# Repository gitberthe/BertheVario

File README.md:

# Projets BertheVario/GnuVario, BertheVarioTac et BertheVario213. 
Vario Gps parapente developés en C/C++ sous Platformio/VisualStudioCode/Code::Blocks (Software). kicad/freecad (Hardware).

**BertheVario/GnuVario :**
- firmware pour GnuVario (https://prunkdump.github.io/GNUVario-TTGO-T5-website/0-Accueil.html)
- carte mere indisponible donc pour mise a jour vario existant uniquement.
- socle pour les fichiers commun des 3 vario.

**BertheVarioTac :**
- Vario a base de ESP32-2432S028 sans la coque.
- un peut lourd pour voler et moindre autonomie d'alimentation.

**BertheVario213 :**
- Vario et coque imprimable 3d a base de Lilygo GDEM0213T5BN.
- le plus abouti des 3 vario.

**Photo des 3 vario :**

**Logiciels annexes :**
- CompZoneAerienne : logiciel pour la creation du fichier de zone aerienne (TMA, CTR...). Visualisation des zones par fichier *.png et *.kml :
- GestHgt : logiciel pour les fichier *.hgt d'altitude sol (filtre france) et creation/verification checksum.
- IgcReader : logiciel pour relire succinctement un fichier igc (Z deco, Z attero ...) et le transformer en .kml pour googleearth.
- igc2kmz : logiciel python disponible sur le web pour creer un fichier .kmz googleearth, a partir d'un .igc (couleur fonction de Vz, altitude...) :

zenodo :
https://doi.org/10.5281/zenodo.18722633

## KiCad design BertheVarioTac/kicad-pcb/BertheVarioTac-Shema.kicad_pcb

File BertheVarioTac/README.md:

# Projet BertheVarioTac ESP32-2432S028
Projet d'alti vario gps parapente tactile (avec gestion des TMA CTR..., et mode guidage sol pour randonnée).
- Code C++ Visual Studio/PlateformIO.
- Plateforme Espressif ESP32 Dev Module, 2.8inch ESP32-2432S028, Arduino, ESP32-WROOM-32,  (processeur LX6 32bits, bi-core 240mhz).

**Utilisation / description :**
- documentation utilisateur et autre dans /documentation
- projet PlateformIO dans /BertheVarioTacPlatformIO
- editer/modifier avec codeblocks dans /Codeblocks
- documentation developpeur dans ../../DoxyBertheVarioTac avec le commande "doxygen Doxyfile.BertheVarioTac" depuis /Codeblocks

**Pour les développeur :**
- voir la documentation doxygen generée.

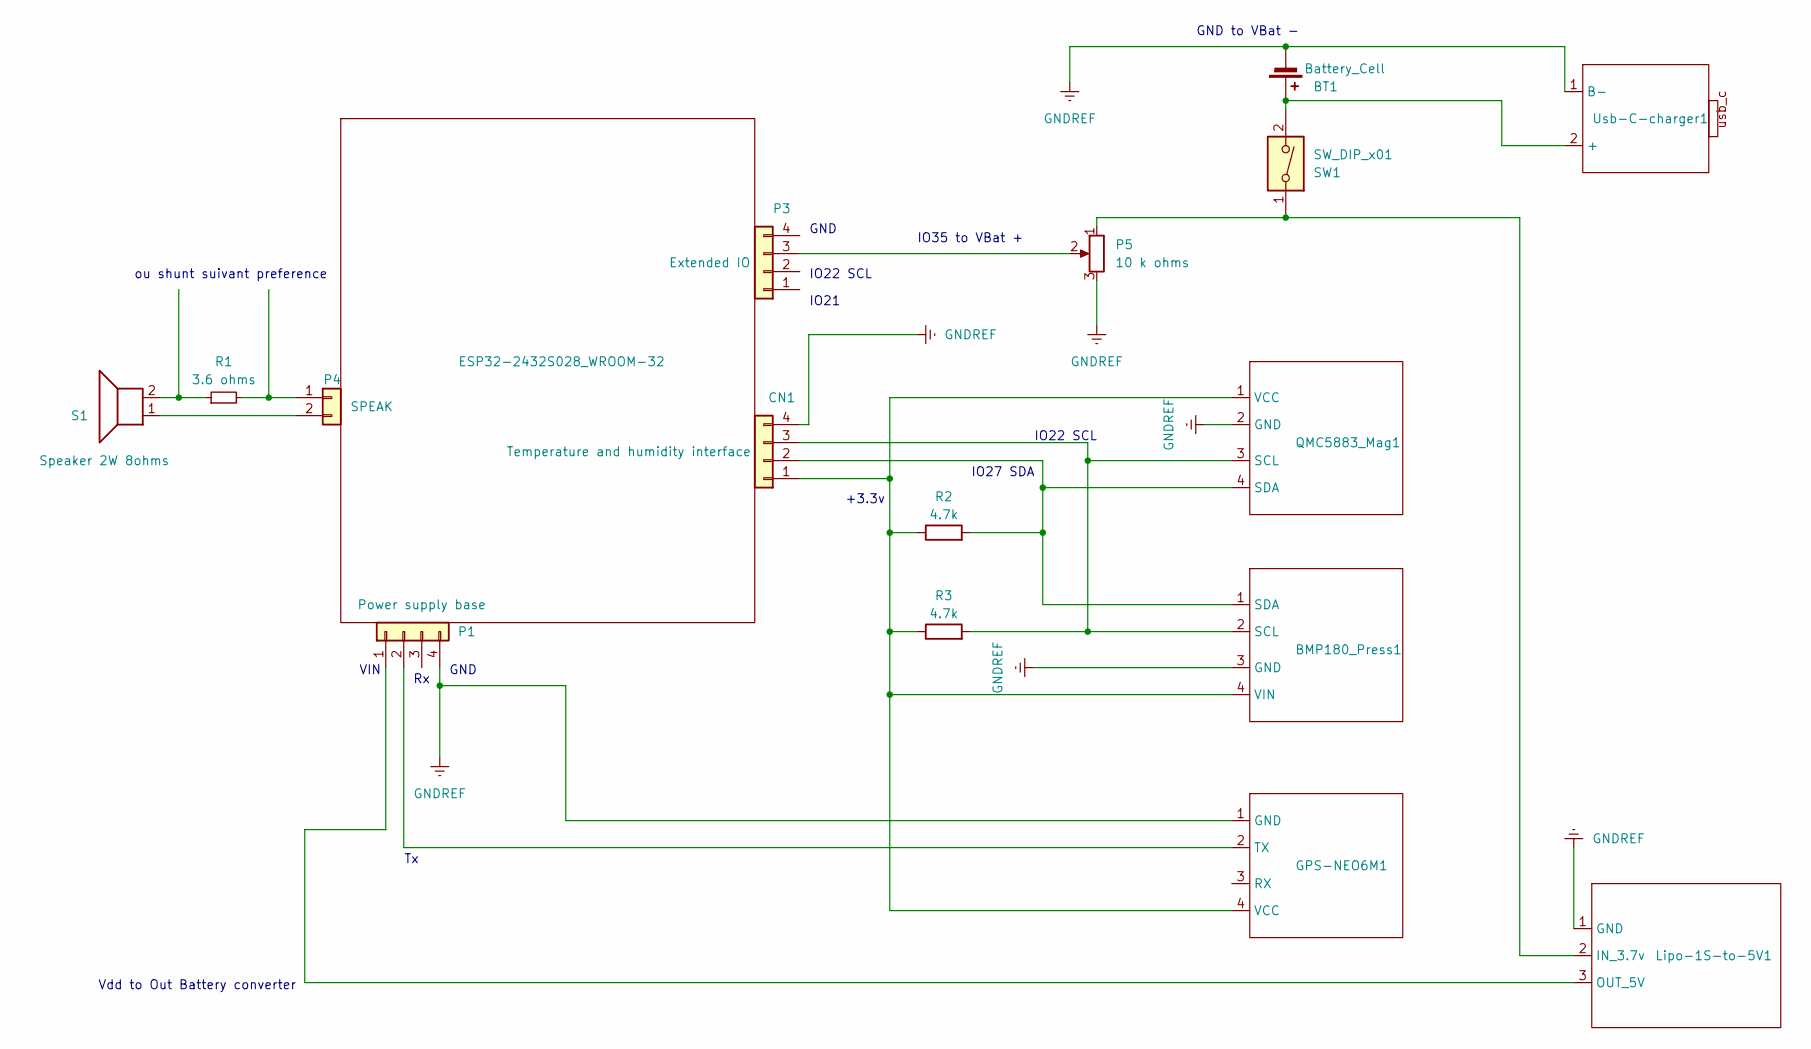
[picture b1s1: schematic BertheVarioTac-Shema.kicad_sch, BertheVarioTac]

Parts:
BMP180_Press1: BMP180
BT1: Battery_Cell; batterie
CN1: Temperature and humidity interface; 4 trous standard
ESP32-2432S028_WROOM-32: -; KiCad-Logo2_5mm_SilkScreen
GPS-NEO6M1: -; GPSNEO6V2
Lipo-1S-to-5V1: -; 1S-to-5v
P1: Power supply base; 4 trous standard
P3: Extended IO; 4 trous standard
P4: SPEAK; 2 trous standard
P5: 10 k ohms; potentiometre
QMC5883_Mag1: QMC5883
R1: 3.6 ohms; R_Axial_DIN0207_L6.3mm_D2.5mm_P10.16mm_Horizontal
R2, R3: 4.7k; R_47
S1: Speaker 2W 8ohms; 2 trous standard
SW1: SW_DIP_x01; 2 trous standard
Usb-C-charger1: -; Usb-C-Charger

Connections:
GNDREF: BMP180_Press1.3 (GND), BT1.2 (-), CN1.4, GPS-NEO6M1.1 (GND), Lipo-1S-to-5V1.1 (GND), P1.4, P5.3, QMC5883_Mag1.2 (GND), Usb-C-charger1.1 (B-)
unnamed: BMP180_Press1.2 (SCL), CN1.3, QMC5883_Mag1.3 (SCL), R3.2
unnamed: BMP180_Press1.1 (SDA), CN1.2, QMC5883_Mag1.4 (SDA), R2.2
unnamed: BMP180_Press1.4 (VIN), CN1.1, GPS-NEO6M1.4 (VCC), QMC5883_Mag1.1 (VCC), R2.1, R3.1
unnamed: BT1.1 (+), SW1.2, Usb-C-charger1.2 (+)
unnamed: GPS-NEO6M1.2 (TX), P1.2
unnamed: Lipo-1S-to-5V1.2 (IN_3.7v), P5.1, SW1.1
unnamed: Lipo-1S-to-5V1.3 (OUT_5V), P1.1
unnamed: P3.3, P5.2
unnamed: P4.1, R1.2
unnamed: P4.2, S1.1
unnamed: R1.1, S1.2

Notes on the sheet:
IO22 SCL
Vdd to Out Battery converter
GND
GND to VBat -
IO27 SDA
IO21
IO35 to VBat +
+3.3v
VIN
ou shunt suivant preference

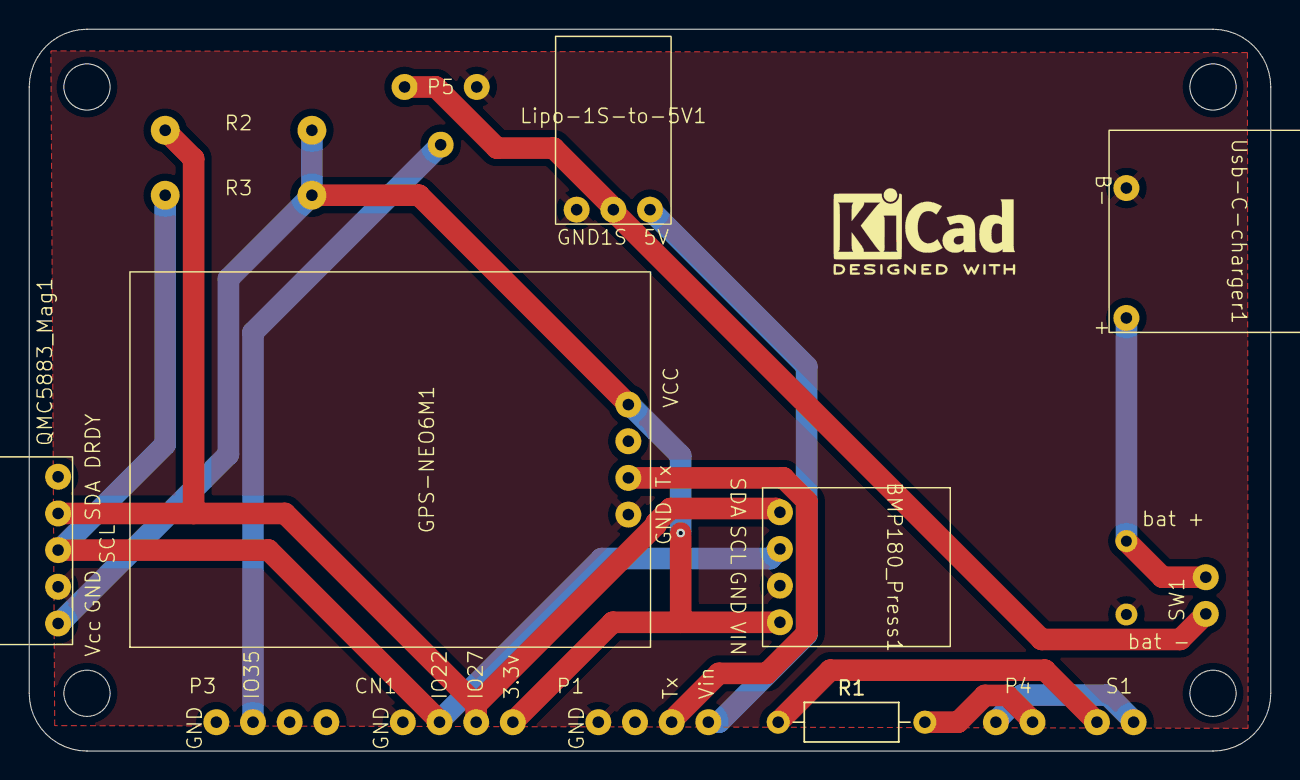
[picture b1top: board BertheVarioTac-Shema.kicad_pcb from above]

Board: 2 copper layers, 86.0 x 50.0 mm, 17 parts (0 on the bottom side), 12 nets.

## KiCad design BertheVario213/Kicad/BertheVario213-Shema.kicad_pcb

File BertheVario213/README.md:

# Projet BertheVario213

Projet d'alti vario gps parapente (avec gestion des TMA CTR..., et mode guidage sol pour randonnée).
- Code C++ Visual Studio/PlateformIO.
- Plateforme Espressif ESP32 Dev Module, LILYGO T5 v2.3.1 GDEM0213T5BN 9102 chip, écran 2.13inch DEPG0213BN, Arduino (processeur 32bits, dual core, 240Mhz).

**La carte avec son pcb :**

**Le schema electrique :**

**Le pcb :**

**Le mode randonnée :**

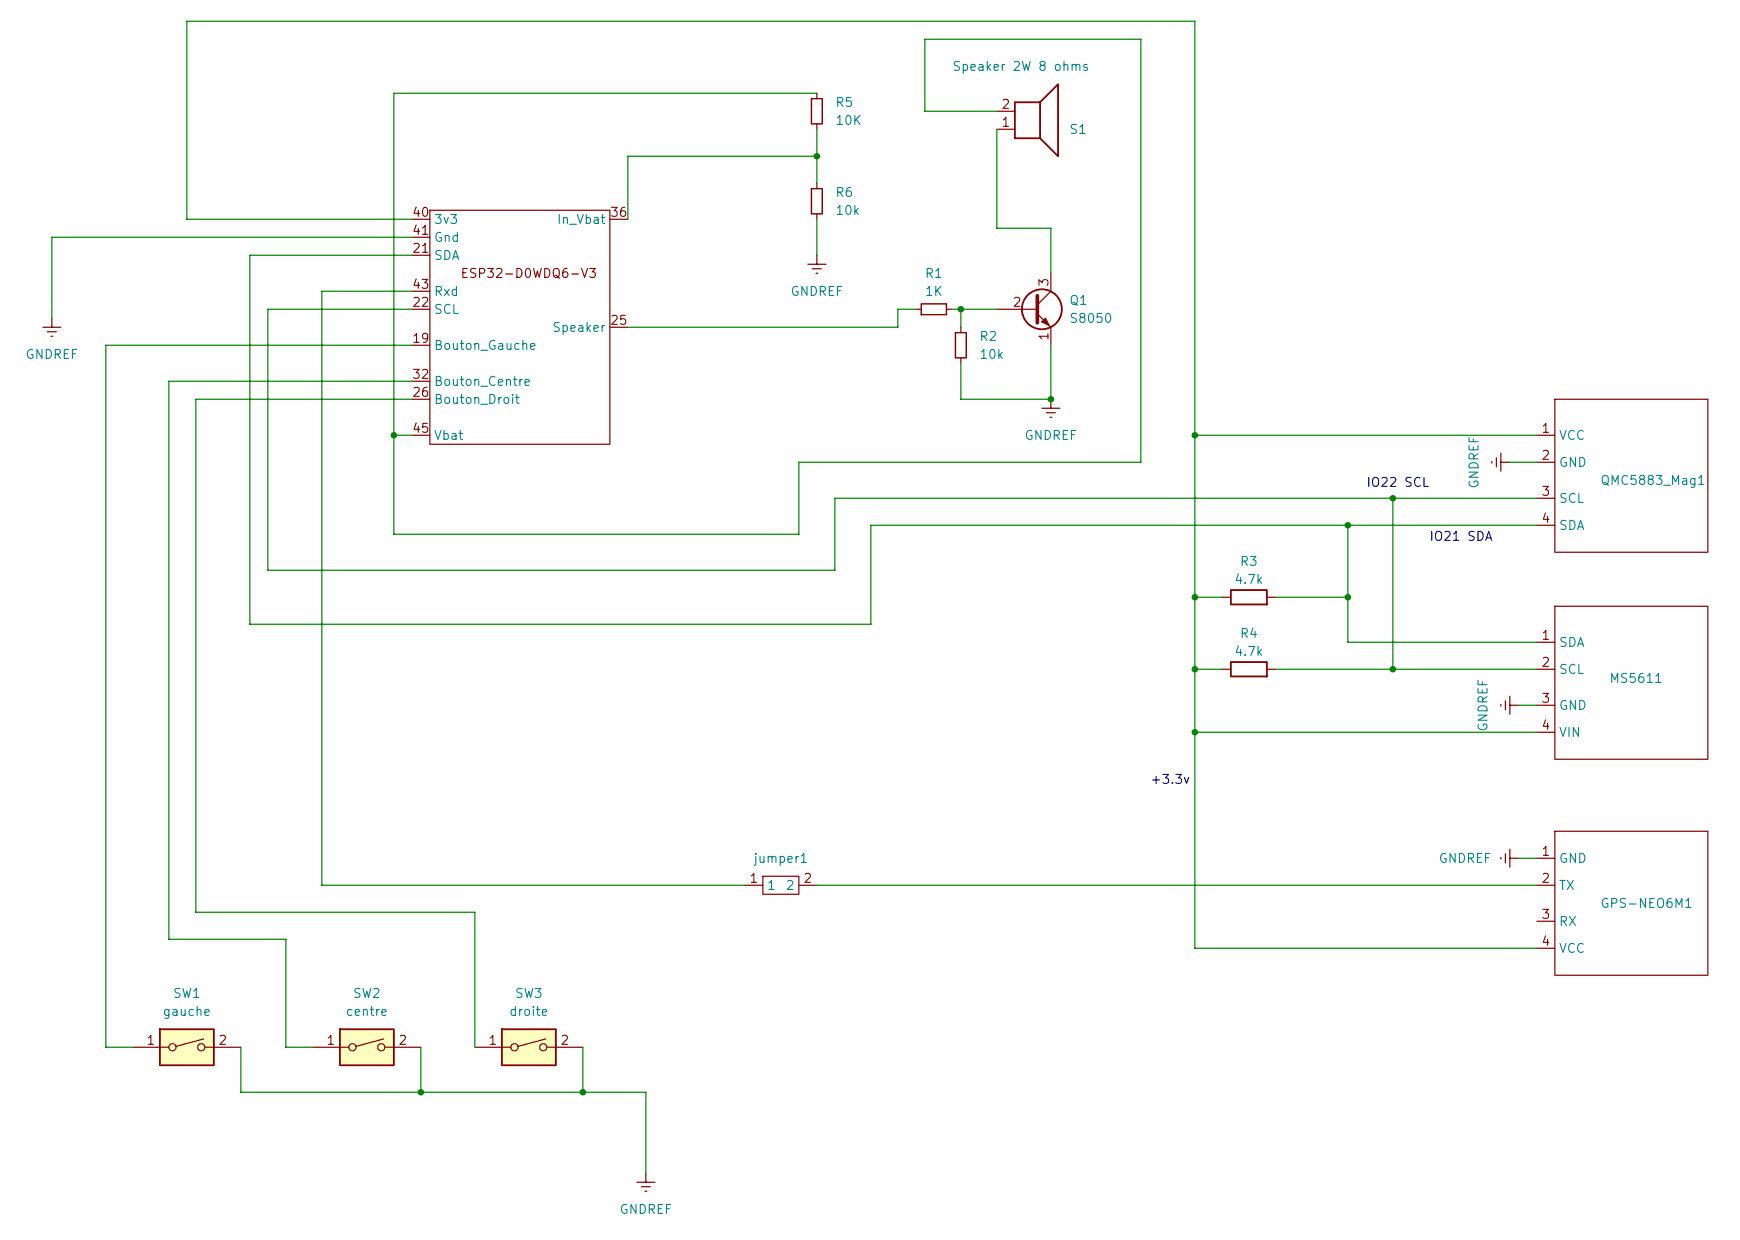
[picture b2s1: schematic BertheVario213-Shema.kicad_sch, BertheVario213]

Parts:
GPS-NEO6M1: -; GPSNEO6V2
MS5611: MS5611
Q1: S8050
QMC5883_Mag1: QMC5883
R1: 1K; R_47
R2, R6: 10k; R_47
R3, R4: 4.7k; R_47
R5: 10K; R_47
S1: Speaker 2W 8 ohms; 2 trous standard
SW1: gauche; switch
SW2: centre; switch
SW3: droite; switch
U1: ESP32-D0WDQ6
jumper1: jumper

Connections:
GNDREF: GPS-NEO6M1.1 (GND), MS5611.3 (GND), Q1.1 (E), QMC5883_Mag1.2 (GND), R2.2, R6.2, SW1.2, SW2.2, SW3.2, U1.41 (Gnd)
unnamed: GPS-NEO6M1.2 (TX), jumper1.2
unnamed: GPS-NEO6M1.4 (VCC), MS5611.4 (VIN), QMC5883_Mag1.1 (VCC), R3.1, R4.1, U1.40 (3v3)
unnamed: MS5611.2 (SCL), QMC5883_Mag1.3 (SCL), R4.2, U1.22 (SCL)
unnamed: MS5611.1 (SDA), QMC5883_Mag1.4 (SDA), R3.2, U1.21 (SDA)
unnamed: Q1.2 (B), R1.2, R2.1
unnamed: Q1.3 (C), S1.1
unnamed: SW2.1, U1.32 (Bouton_Centre)
unnamed: SW3.1, U1.26 (Bouton_Droit)
unnamed: SW1.1, U1.19 (Bouton_Gauche)
unnamed: R5.2, R6.1, U1.36 (In_Vbat)
unnamed: U1.43 (Rxd), jumper1.1
unnamed: R1.1, U1.25 (Speaker)
unnamed: R5.1, S1.2, U1.45 (Vbat)

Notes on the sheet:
IO22 SCL
IO21 SDA
+3.3v

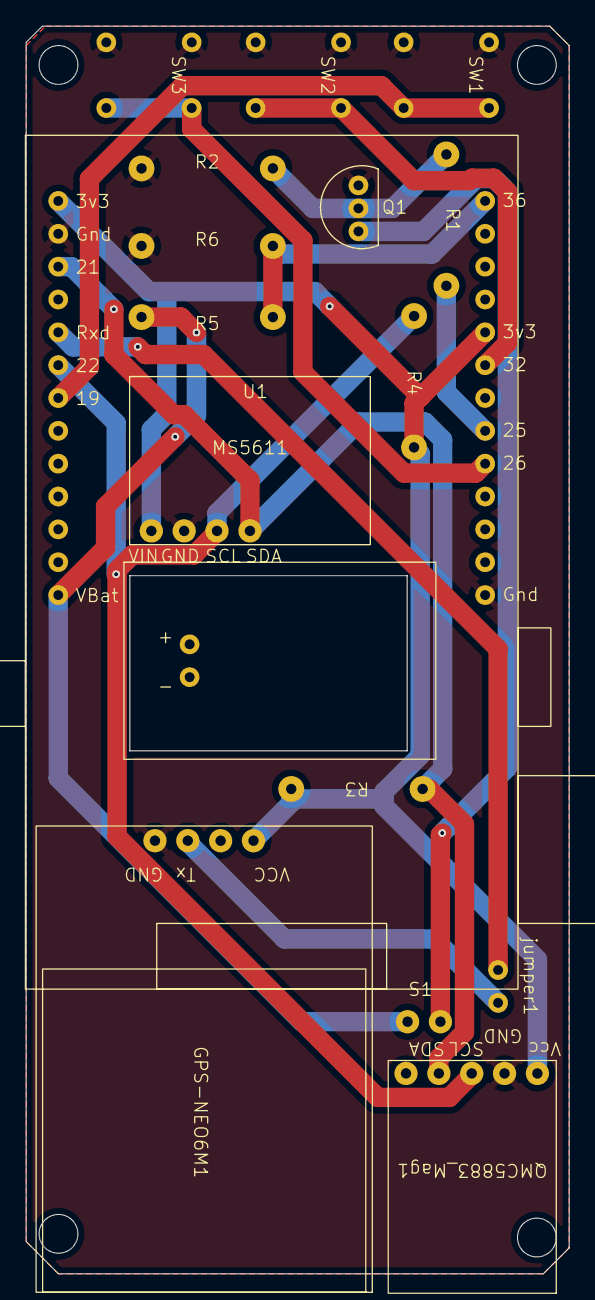
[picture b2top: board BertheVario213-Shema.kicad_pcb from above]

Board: 2 copper layers, 42.0 x 96.5 mm, 16 parts (0 on the bottom side), 14 nets.

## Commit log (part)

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2024-04-14 modification pour developpeur doc et readme
2024-04-14 correction bug pour version 20240414a
2024-04-14 ajout pour correction bug pour version 20240414a
2024-04-15 modification cpateur magnetique et ecran
2024-04-15 modification capteur magnetique et ecran
2024-04-15 modification doxygen
2024-04-15 modification notam.py a faire dans readme.txt
2024-04-26 condition reboot vitesse petite
2024-04-26 condition reboot position < +-30m et alti < +-0.5m
2024-05-13 modification visu en ascendance
2024-06-02 modif condition debut de vol 5s
2024-06-06 declenchement vol ecran 0_Vz
2024-06-06 changement de page GD ecran 0_Vz
2024-06-07 plus de memorisation bouton B depart de vol en G/S
2024-06-07 plus de memorisation bouton droit depart de vol en G/S
2024-06-07 modification sons accrochage gps
2024-06-14 son G V S 5 secondes
2024-06-17 valeurs par defaut config.txt
2024-07-14 modification son vario
2024-07-14 modification son vario/fichier config
2024-07-15 modif zone activable protect
2024-07-15 doublons dans fichier zone activable
2024-07-15 suppression doublons affichage zone activable
2024-07-20 modification zones et termic
2024-07-20 optimization memoire et zone
2024-07-21 optimization memoire zone
2024-07-21 conditions declenchement vol
2024-07-21 + ou - vz_igc_ms
2024-07-27 alti baro + ecran igc
2024-07-27 correction documentation
2024-07-27 modification menu zones activable
2024-07-28 corretion de doc openoffice/pdf
2024-07-28 correction de doc openoffice/pdf
2024-07-28 hauteur sol
2024-08-07 valeur par defaut config.txt
2024-08-08 archivage/historique des igc
2024-08-09 ihm et fin de vol
2024-08-09 non archivage si vol < 1min
2024-08-09 non archivage si vol < 1min et bug
2024-08-10 correction temporaire bug Vz
2024-08-12 correction Vz bloquée a zero et doc
2024-08-12 correction Vz bloquée a zero et documentation
2024-08-13 Calcul TMA, faux depart de vol cause xy
2024-08-13 raz ecran quand retour vz_0
2024-08-16 valeur par defaut fichier de configuration
2024-08-22 son pour zerotage
2024-08-23 son zerotage et bugs
2024-08-24 fin de vol automatique
2024-08-24 vitesse verticale CFinDeVol
2024-08-27 reset capteur pression
2024-08-29 reset capteur pression MS5611
2024-09-02 nombre de satellites
2024-09-03 boucle arret/debut de vol
2024-09-04 calcul somme temps igc
2024-09-04 modification documentation
2024-09-04 son zerotage
2024-09-05 ajout sat_sec dans config
2024-09-06 modification doc
2024-09-20 bug recalage altibaro
2024-09-28 refonte calcul zone
2024-10-04 son zone/vario
2024-10-04 altitude sol ouest fausse
2024-10-05 bug desactivation alarme sonore zone
2024-10-06 modification [temp_igc_sec] par defaut
2024-10-08 [vz_igc_ms] pendant 3s
2024-10-12 [temps_igc_ms] et [sat_sec]
2024-10-12 [temps_igc_sec] et [sat_sec]
2024-10-15 [sat_sec] 10s
2024-10-19 modif raz screen
2024-10-20 modif sat_sec delay
2024-10-24 [temps_igc_sec] 4s
2024-10-25 memorisation cap
2024-10-26 [sat_sec] et CFinDeVol
2024-11-17 affichage page Vz
2024-11-17 optimisation memoire
2024-11-20 gain memoire
2024-11-20 Vz plus reactif
2024-11-22 [coef_filtre_alti_baro] à 0.8
2024-11-26 gros gain memoire zones
2024-11-26 reduction zone dans BVZoneAeriennegit add !!!
2024-11-26 reduction zone dans BVZoneAerienne !!!
2024-11-26 bug fuite memoire
2024-11-28 nouveaux zonesaer.txt
2024-11-29 ajout CompZoneAerienne
2024-11-29 modif zonesaer.txt
2024-11-30 decimales zonesaer.txt
2024-11-30 erreur moyenne
2024-12-01 CompZoneAerienne et zone protege
2024-12-01 resolution zone 10m
2024-12-01 firmware
2024-12-01 calcul de zone
2024-12-01 resolution variable
2024-12-02 zone protect
2024-12-02 firmware doc
2024-12-02 doc readme.md
2024-12-02 readme.md
2024-12-03 gain memoire zone
2024-12-04 bug zoneaer.txt
2024-12-05 structuration CompZoneAerienne
2024-12-09 CompZoneAerienne.exe W10
2024-12-12 affichage rapide temps froid
2024-12-21 bug magnetique
2024-12-29 modif platform
2024-12-29 modif readme
2024-12-29 modif documentation
2025-01-08 ecran plus rapide?
2025-01-09 temps froid ameliore
2025-01-10 bug nom zone RTBA
2025-01-10 nom zone ffvl/protect
2025-01-10 congelateur ok
2025-01-11 ctr rodez
2025-01-11 correction doc
2025-01-12 memorisation point gps
2025-01-12 stationnaire non bloquant
2025-01-13 sound server
2025-01-13 developement futur
2025-01-13 bug vz fausse defois
2025-01-13 ebauche rando-vol
2025-01-14 menu rando-vol
2025-01-14 rando-vol ok
2025-01-14 cap gps rando
2025-01-14 echelle rando
2025-01-15 menu rando
2025-01-15 altitude gpx
2025-01-15 page info rando
2025-01-17 affichage different
2025-01-18 affichage bien propre
2025-01-18 guidage rando terrain connu
2025-01-18 appui long centre
2025-01-18 ihm zone
2025-01-18 reboot GD
2025-01-18 appui court boot
2025-01-19 temp raz
2025-01-20 ptremarq.txt
2025-01-20 rando cap gps
2025-01-20 raz ecran froid
2025-01-20 fuite memoire
2025-01-20 double appui
2025-01-20 timing double appui
2025-01-20 harmonisation touches
2025-01-21 messages boutons
2025-01-21 temps vol float
2025-01-21 raz ecran
2025-01-21 maj bibliotheques
2025-01-21 affichage hauteur sol
2025-01-22 commentaire
2025-01-24 affichage igc
2025-01-27 suppression double appui
2025-01-29 modification plateforme
2025-01-29 beep demarrage
2025-01-29 page Vz en vol
2025-02-03 hauteur zone protect
2025-02-03 bluetooth XC Track
2025-02-04 XCTrack
2025-02-06 penetration zone 2hz
2025-02-06 modification commentaire code
2025-02-07 bug alarme frontiere zone
2025-02-07 gros bug zone
2025-02-07 algo calc zone
2025-02-07 fuite mem ~CZoneAer()
2025-02-08 altitude/distance/cap prochaine TMA
2025-02-08 pas de zone protege pour prochaine TMA
2025-02-08 bug zone protege
2025-02-09 modif ihm Vz
2025-02-09 beep zone
2025-02-10 ihm tma proche
2025-02-12 zone proche corent
2025-02-12 zone corent
2025-02-14 mail notam
2025-02-14 version doc
2025-02-16 pourcentage batterie
2025-02-25 bug periode tma st-yan
2025-02-25 bug mauvais zonesper.txt
2025-02-25 mise a jour doc
2025-02-25 mise a jour firmware
2025-03-01 valid tma st-yan
2025-03-02 variable calc zone
2025-03-02 bug tma st-yan
2025-03-13 xc_track et 2 Vz consecutives
2025-03-15 alarme XY saint-sandoux
2025-03-22 doc utilisateur
2025-03-25 debut/arret du vol
2025-03-27 priorite tache ecriture fichier
2025-03-27 tache/fichier igc histo
2026-02-20 premier git 3 vario
2026-02-20 modification readme.md
2026-02-21 ajout licence
2026-02-21 rm *.a/o/obj BertheVarioTac Demo
2026-02-21 zenodo doi
2026-02-22 ajout trace photo
2026-02-22 modification readme
2026-02-22 essai firmware.bin tac
2026-02-23 regroupement zones Tac
2026-02-26 hauteur ettero et son
2026-02-27 compensation temperature
2026-03-01 calcul altitude
2026-03-02 nombre de points
2026-03-25 HAUTEUR_LOIN_DECO_METRE a 10m
2026-05-18 tailles piles et buffer gps
2026-06-10 delais init SDCard
2026-06-11 changement de file manager
2026-06-13 erreur fichier hgt
2026-06-13 erreur hgt pas d'igc
2026-06-22 ecran de boot
